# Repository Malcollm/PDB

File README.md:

# Humanoid Robot Power Distribution Board

This repository contains the power distribution board design for the Wiscohumanoids humanoid robot. The board distributes the main battery power to the robot’s high-current actuator system and generates regulated lower-voltage rails for compute, servos, sensors, and control electronics.

The PDB is designed around a 48 V main power system with onboard regulation for the robot’s auxiliary electronics.

## Project Overview

The power distribution board is responsible for taking the main battery input and safely distributing power throughout the robot. It includes high-current 48 V distribution, onboard buck converters, current sensing, precharge circuitry, and protection/disconnect circuitry.

The main goals of this board are:

- Distribute 48 V battery power to actuator rails
- Generate a 24 V compute rail
- Generate a 6 V servo rail for the robot hands
- Generate a 3.3 V rail for sensors and control electronics
- Monitor current on important power paths
- Limit inrush current during startup using precharge circuitry
- Separate actuator/servo power from compute/control power through protection and disconnect circuitry
- Protect the electrical system from voltage transients and fault conditions

## System Power Architecture

```text
Battery Input
    |
    |-- Precharge Circuit
    |
    |-- Main 48 V Power Rail
            |
            |-- Protection / Disconnect Circuitry
                    |
                    |-- Actuator / Servo Power Group
                    |       |
                    |       |-- 48 V Actuator Distribution
                    |       |
                    |       |-- 48 V to 6 V Buck Converter
                    |               |
                    |               |-- Hand Servos
                    |
                    |-- Compute / Control Power Group
                            |
                            |-- 48 V to 24 V Buck Converter
                            |       |
                            |       |-- Compute / Embedded Electronics
                            |
                            |-- 48 V to 3.3 V Buck Converter
                                    |
                                    |-- Sensors / Current Sensors / Control Logic
```

## Power Rails

| Rail | Purpose |
|---|---|
| 48 V | Main battery rail and actuator power distribution |
| 24 V | Compute and embedded electronics |
| 6 V | Servo motors in the robot hands |
| 3.3 V | Sensors, current sensors, and control logic |

## Major Board Features

### 48 V Actuator Distribution

The main power path distributes 48 V battery power to the robot’s actuator system. Because this rail carries the highest current on the board, the layout uses large copper pours, short current paths, and high-current connectors.

This section of the board is designed to minimize voltage drop and reduce heating under actuator load.

### Precharge Circuit

The board includes a precharge circuit to limit inrush current when the battery is connected. This is important because the board contains large bulk capacitance on the main 48 V rail.

During startup, the precharge path slowly charges the bulk capacitors before the main power path is fully enabled. This reduces stress on connectors, switches, relays, and other power components.

### Protection and Disconnect Circuitry

The PDB includes protection and disconnect circuitry that separates the main power system into two groups: the actuator/servo power group and the compute/control power group.

The actuator/servo group contains the 48 V actuator distribution and the 6 V hand servo rail. This group can be disconnected from the rest of the system so high-power motion components can be shut down independently.

The compute/control group contains the 12 V and 3.3 V rails. This allows the robot’s control electronics, sensors, and compute hardware to remain separated from the high-power actuator section.

This separation is important because it allows actuator power to be disabled while keeping control electronics available for monitoring, communication, and safe shutdown behavior.

Protection features include:

- Input transient voltage protection
- Precharge/inrush-current limiting
- Separation between actuator/servo power and compute/control power
- Reverse-current blocking where needed
- Current sensing for fault monitoring
- Support for external E-stop or main disconnect circuitry
- Bulk capacitance for load transients

### Current Sensing

Current sensors are included on important power paths so the robot can monitor how much current different parts of the system are drawing.

Current measurement is useful for:

- Detecting abnormal load conditions
- Debugging actuator behavior
- Estimating power usage
- Monitoring system health
- Adding future fault-detection logic

### Buck Converters

The PDB generates the lower-voltage rails from the main 48 V battery input using buck converters.

The onboard regulated rails are:

- 12 V for compute and embedded electronics
- 6 V for hand servos
- 3.3 V for sensors and control electronics

Each buck converter section includes the switching regulator circuit, input capacitance, output capacitance, feedback network, and supporting passives.

## Grounding

The board uses separate ground naming to keep high-current power paths and sensitive measurement/control paths organized.

Typical ground nets include:

| Net | Purpose |
|---|---|
| PGND | High-current power ground and switching converter return |
| AGND | Analog/sensor ground for feedback and current measurement circuits |

These grounds are not meant to be completely isolated systems. Instead, the separate names help control where large return currents flow and help keep sensor and feedback references cleaner.

## Design Status

This project is currently in development.

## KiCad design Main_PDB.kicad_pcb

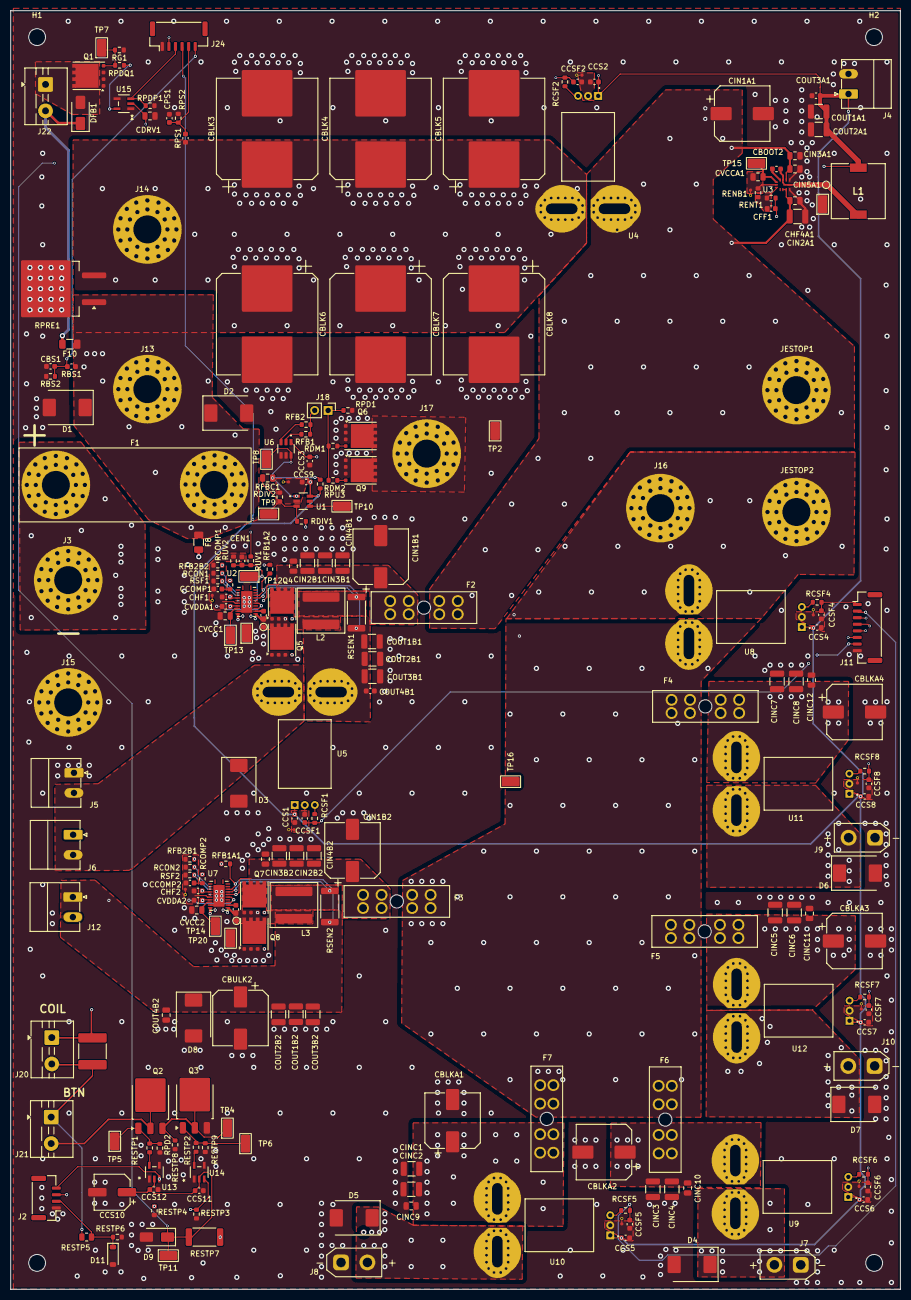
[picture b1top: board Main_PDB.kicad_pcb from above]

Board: 6 copper layers, 168.6 x 242.3 mm, 241 parts (0 on the bottom side), 105 nets.

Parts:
CBLK3, CBLK4, CBLK5, CBLK6, CBLK7, CBLK8: 470u; CP_Elec_18x22
CBLKA1, CBLKA2: 100uF; CP_Elec_10x10
CBLKA3, CBLKA4: 47uF; CP_Elec_10x10
CBOOT1, CBOOT3: 100n; C_0603_1608Metric
CBOOT2: 100nF; C_0603_1608Metric
CBS1: 100nF; C_0603_1608Metric
CBULK2: 100uF; CP_Elec_10x10
CCOMP1: 2nF; C_0603_1608Metric
CCOMP2: 2.7nF; C_0603_1608Metric
CCS1, CCS2, CCS3, CCS4, CCS5, CCS6, CCS7, CCS8, CCS9: 100n; C_0603_1608Metric
CCS10: 100uF 35V; CP_Elec_6.3x5.4
CCS11, CCS12: 100nF 50V; C_0603_1608Metric
CCSF1, CCSF2, CCSF4, CCSF5, CCSF6, CCSF7, CCSF8: 10n; C_0603_1608Metric
CDRV1: 1uF; C_0805_2012Metric
CEN1: 1nF; C_0603_1608Metric
CFF1: 22pF; C_0603_1608Metric
CHF1, CHF2: 22pF; C_0603_1608Metric
CHF4A1: 220nF; C_0805_2012Metric
CIN1A1, CIN1B1: 47uF; CP_Elec_10x10
CIN1B2: 100uF; CP_Elec_10x10
CIN2A1: 4.7uF; C_1210_3225Metric
CIN2B1, CIN2B2, CIN3B1, CIN3B2, CIN4B1, CIN4B2: 4.7u; C_1210_3225Metric
CIN3A1: 220nF; C_0805_2012Metric
CIN5A1, CIN5B1, CIN5B2: 100nF; C_0805_2012Metric
CINC1, CINC2, CINC3, CINC4, CINC5, CINC6, CINC7, CINC8: 4.7u; C_1210_3225Metric
CINC9, CINC10, CINC11, CINC12: 100nF; C_0805_2012Metric
COUT1A1, COUT2A1: 47uF; C_1210_3225Metric
COUT1B1, COUT1B2, COUT2B1, COUT2B2, COUT3B1, COUT3B2: 22uF; C_1210_3225Metric
COUT3A1, COUT4B1: 100nF; C_0603_1608Metric
COUT4B2: 100nF; C_0805_2012Metric
CPS1: 100nF; C_0603_1608Metric
CVCC1, CVCC2: 2.2u; C_0805_2012Metric
CVCCA1: 1uF; C_0805_2012Metric
CVDDA1, CVDDA2: 100n; C_0603_1608Metric
D1, D2, D3, D4, D5, D6, D7, D8: TVS; D_SMC
D9: 12V Zener 1W; D_SMA
D11: 3.3V Zener; D_SOD-123
DFB1: S1M; D_SMA
F1: Fuse; FUSE_BF1_M5_100A
F2, F3, F4, F5, F6, F7: LITTELFUSE_178.6165.0002
F8, F10: 0.5A; Fuse_1206_3216Metric
H1, H2, H3, H4: MountingHole_3.2mm_M3
J2: Conn_01x04; JST_GH_BM04B-GHS-TBT_1x04-1MP_P1.25mm_Vertical
J3: Conn_Batt_PWR; MountingHole_5.3mm_M5_Pad_Via_HP
J4: 3.3V Out; PhoenixContact_MC_1,5_2-G-3.81_1x02_P3.81mm_Horizontal
J5: 24V Out -> Jetson; PhoenixContact_MC_1,5_2-G-3.81_1x02_P3.81mm_Horizontal
J6: 24V Out -> USB-C-PD controller; PhoenixContact_MC_1,5_2-G-3.81_1x02_P3.81mm_Horizontal
J7, J8, J9, J10: Conn_01x02; AMASS_XT30UPB-F_1x02_P5.0mm_Vertical
J11: Conn_01x08; JST_GH_BM08B-GHS-TBT_1x08-1MP_P1.25mm_Vertical
J12: 6V Out; PhoenixContact_MC_1,5_2-G-3.81_1x02_P3.81mm_Horizontal
J13: PRECIN; MountingHole_5.3mm_M5_Pad_Via_HP
J14: PRECOUT; MountingHole_5.3mm_M5_Pad_Via_HP
J15: Conn_Batt_GND; MountingHole_5.3mm_M5_Pad_Via_HP
J16: Dump_Resistor_In; MountingHole_5.3mm_M5_Pad_Via_HP
J17: Dump_Resistor_Out; MountingHole_5.3mm_M5_Pad_Via_HP
J18: BC_Disconnect; PinHeader_1x02_P2.54mm_Vertical
J20: ESTOP Contactor Coil Control; TerminalBlock_MaiXu_MX126-5.0-02P_1x02_P5.00mm
J21: ESTOP Button (Normally Closed); TerminalBlock_MaiXu_MX126-5.0-02P_1x02_P5.00mm
J22: Precharge Contactor Coil Control; TerminalBlock_MaiXu_MX126-5.0-02P_1x02_P5.00mm
J24: Precharge Ctrl In; JST_GH_BM06B-GHS-TBT_1x06-1MP_P1.25mm_Vertical
JESTOP1: ESTOP_IN; MountingHole_5.3mm_M5_Pad_Via_HP
JESTOP2: ESTOP_OUT; MountingHole_5.3mm_M5_Pad_Via_HP
L1: 18uH; L_Sumida_CDRH104R
L2: 10uH; L_Coilcraft_XAL8080-XXX
L3: 4.7uH; L_Coilcraft_XAL8080-XXX
NT1, NT2, NT3, NT4, NT5, NT6, NT7, NT8, NT9, NT10, NT11: NetTie_2; NetTie_AGND_PGND_VIA
Q1, Q5, Q6, Q8, Q9: BSC070N10LS5ATMA1; VSONP-8-1EP_5x6_P1.27mm
Q2, Q3: NMOS IRFR220N; TO-252-3_TabPin2
Q4, Q7: BSC146N10LS5; VSONP-8-1EP_5x6_P1.27mm
RBS1: 100k; C_0603_1608Metric
RBS2: 3.9k; R_0603_1608Metric
RCOMP1: 19.1k; R_0603_1608Metric
RCOMP2: 12.1k; R_0603_1608Metric
RCON1, RCON2: 41.2k; R_0603_1608Metric
RCSF1, RCSF2, RCSF4, RCSF5, RCSF6, RCSF7, RCSF8: 1k; R_0603_1608Metric
RDIV1: 1M; R_0603_1608Metric
RDIV2: 24k; R_0603_1608Metric
RDM1, RDM2: 2.2R; R_0603_1608Metric
RENB1: 43.2k; R_0603_1608Metric
RENT1: 100k; R_0603_1608Metric
RESTP1, RESTP2: 100R; R_0603_1608Metric
RESTP3, RESTP4: 2.2k; R_0603_1608Metric
RESTP5: 100k; R_0805_2012Metric
RESTP6: 7.5k; R_0603_1608Metric
RESTP7: 4.7K 1W; R_2512_6332Metric
RESTP8, RESTP9: 100k; R_0603_1608Metric
RFB1, RFB2: 4.7R; R_0603_1608Metric
RFB1A1: 64.9k; R_0603_1608Metric
RFB1A2: 291k; R_0603_1608Metric
RFB2B1, RFB2B2: 10k; R_0603_1608Metric
RFBC1: 1.65M; C_0805_2012Metric
RG1: 100R; R_0603_1608Metric
RPD1, RPD2: 100k; R_0603_1608Metric
RPDP1: 100k; R_0603_1608Metric
RPDQ1: 100k; R_0603_1608Metric
RPRE1: 100; TO-263-2_Resistor
RPS1: 100k; C_0603_1608Metric
RPS2: 3.9k; R_0603_1608Metric
RPU3: 10k; R_0603_1608Metric
RSEN1, RSEN2: 0.004R; R_2512_6332Metric
RSF1, RSF2: 47k; R_0603_1608Metric
RUV1, RUV2: 100k; R_0603_1608Metric
TP1, TP2, TP3, TP4, TP5, TP6, TP7, TP8, TP9, TP10, TP11, TP12, TP13, TP14, TP15, TP16: Keystone 5015; TestPoint_Keystone_5015_Micro_Mini
TP17, TP18, TP19: SW probe pad; TestPoint_Pad_D1.0mm
TP20: PGND probe pad; TestPoint_Keystone_5015_Micro_Mini
U1: TLV3011AIDBVT; SOT95P280X145-6N
U2, U7: LM5148RGYR; QFN50P550X350X100-25N
U3: LMR36015ARNXR; RNX0012B
U4, U5, U8, U9, U10, U11, U12: ACS758LCB-100B-PFF-T; XDCR_ACS758LCB-100U-PFF-T
U6: UCC27511DBVR; SOT95P280X145-6N
U13, U14, U15: MCP1402T-E/OT; SOT-23-5_MC_MCH
ZV50K2220801NIR1: Varistor; C_2220_5750Metric

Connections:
+3.3V: CCS1.1, CCS2.2, CCS4.2, CCS5.1, CCS6.1, CCS7.1, CCS8.1, CCS9.1, CFF1.1, COUT1A1.1, COUT2A1.1, COUT3A1.1, J4.1, J24.2, L1.2, RENT1.1, RPU3.2, U1.6 (V+), U4.1 (VCC), U5.1 (VCC), U8.1 (VCC), U9.1 (VCC), U10.1 (VCC), U11.1 (VCC), U12.1 (VCC)
+6V: CBULK2.1, CCS3.1, COUT1B2.1, COUT2B2.1, COUT3B2.1, COUT4B2.1, D8.1 (K), J12.1, RFB1A1.2, RSEN2.2, U6.1 (VDD), U7.21 (VOUT)
+6V_IND: L3.2, RSEN2.1, U7.20 (ISNS+)
+24V: D3.1 (K), J5.2, J6.2, U5.5 (IP-), U5.5_1 (IP-), U5.5_2 (IP-), U5.5_3 (IP-), U5.5_4 (IP-), U5.5_5 (IP-), U5.5_6 (IP-), U5.5_7 (IP-), U5.5_8 (IP-), U5.5_9 (IP-), U5.5_10 (IP-), U5.5_11 (IP-), U5.5_12 (IP-), U5.5_13 (IP-), U5.5_14 (IP-), U5.5_15 (IP-), U5.5_16 (IP-)
+48V_BATT: F1.1, J3.1 (Pin_1_1)
/3V3_SW: CBOOT2.2, L1.1, TP19.1 (1_1), U3.3 (NC), U3.12 (SW)
/3V3_VCC: CVCCA1.2, TP15.1 (1_1), U3.5 (VCC)
/6V_FUSE: CIN1B2.1, CIN2B2.2, CIN3B2.2, CIN4B2.2, CIN5B2.2, F3.2_1, F3.2_2, F3.2_3, F3.2_4, Q7.3 (D), U7.12 (VIN), U7.19 (EN)
/6V_NMOS: CBOOT3.1, L3.1, Q7.1 (S), Q8.3 (D), TP18.1 (1_1), U7.14 (SW)
/6V_VCC: CVCC2.1, TP14.1 (1_1), U7.9 (VCC)
/12V_BIAS: CCS10.1, CCS11.2, CCS12.2, CDRV1.1, D9.1 (K), RESTP7.2, TP11.1 (1_1), U13.2 (VDD), U14.2 (VDD), U15.2 (VDD)
/24V_EN: CEN1.1, RUV1.2, RUV2.1, TP12.1 (1_1), U2.19 (EN)
/24V_EN_IN: J24.4, RUV1.1
/24V_FUSE: CIN1B1.1, CIN2B1.2, CIN3B1.2, CIN4B1.2, CIN5B1.2, F2.2_1, F2.2_2, F2.2_3, F2.2_4, Q4.3 (D), U2.12 (VIN)
/24V_IND: L2.2, RSEN1.1, U2.20 (ISNS+)
/24V_NMOS: CBOOT1.2, L2.1, Q4.1 (S), Q5.3 (D), TP17.1 (1_1), U2.14 (SW)
/24V_SEN: COUT1B1.1, COUT2B1.1, COUT3B1.1, COUT4B1.1, RFB1A2.2, RSEN1.2, U2.21 (VOUT), U5.4 (IP+), U5.4_1 (IP+), U5.4_2 (IP+), U5.4_3 (IP+), U5.4_4 (IP+), U5.4_5 (IP+), U5.4_6 (IP+), U5.4_7 (IP+), U5.4_8 (IP+), U5.4_9 (IP+), U5.4_10 (IP+), U5.4_11 (IP+), U5.4_12 (IP+), U5.4_13 (IP+), U5.4_14 (IP+), U5.4_15 (IP+), U5.4_16 (IP+)
/24V_VCC: CVCC1.1, TP13.1 (1_1), U2.9 (VCC)
/48V_ACT: F3.1_1, F3.1_2, F3.1_3, F3.1_4, F4.1_1, F4.1_2, F4.1_3, F4.1_4, F5.1_1, F5.1_2, F5.1_3, F5.1_4, F6.1_1, F6.1_2, F6.1_3, F6.1_4, F7.1_1, F7.1_2, F7.1_3, F7.1_4, U8.5 (IP-), U8.5_1 (IP-), U8.5_2 (IP-), U8.5_3 (IP-), U8.5_4 (IP-), U8.5_5 (IP-), U8.5_6 (IP-), U8.5_7 (IP-), U8.5_8 (IP-), U8.5_9 (IP-), U8.5_10 (IP-), U8.5_11 (IP-), U8.5_12 (IP-), U8.5_13 (IP-), U8.5_14 (IP-), U8.5_15 (IP-), U8.5_16 (IP-)
/48V_ACT1: D5.1 (K), J8.2, U10.5 (IP-), U10.5_1 (IP-), U10.5_2 (IP-), U10.5_3 (IP-), U10.5_4 (IP-), U10.5_5 (IP-), U10.5_6 (IP-), U10.5_7 (IP-), U10.5_8 (IP-), U10.5_9 (IP-), U10.5_10 (IP-), U10.5_11 (IP-), U10.5_12 (IP-), U10.5_13 (IP-), U10.5_14 (IP-), U10.5_15 (IP-), U10.5_16 (IP-)
/48V_ACT1_FUSE: CBLKA1.1, CINC1.2, CINC2.2, CINC9.1, F7.2_1, F7.2_2, F7.2_3, F7.2_4, U10.4 (IP+), U10.4_1 (IP+), U10.4_2 (IP+), U10.4_3 (IP+), U10.4_4 (IP+), U10.4_5 (IP+), U10.4_6 (IP+), U10.4_7 (IP+), U10.4_8 (IP+), U10.4_9 (IP+), U10.4_10 (IP+), U10.4_11 (IP+), U10.4_12 (IP+), U10.4_13 (IP+), U10.4_14 (IP+), U10.4_15 (IP+), U10.4_16 (IP+)
/48V_ACT2: D4.1 (K), J7.2, U9.5 (IP-), U9.5_1 (IP-), U9.5_2 (IP-), U9.5_3 (IP-), U9.5_4 (IP-), U9.5_5 (IP-), U9.5_6 (IP-), U9.5_7 (IP-), U9.5_8 (IP-), U9.5_9 (IP-), U9.5_10 (IP-), U9.5_11 (IP-), U9.5_12 (IP-), U9.5_13 (IP-), U9.5_14 (IP-), U9.5_15 (IP-), U9.5_16 (IP-)
/48V_ACT2_FUSE: CBLKA2.1, CINC3.2, CINC4.2, CINC10.1, F6.2_1, F6.2_2, F6.2_3, F6.2_4, U9.4 (IP+), U9.4_1 (IP+), U9.4_2 (IP+), U9.4_3 (IP+), U9.4_4 (IP+), U9.4_5 (IP+), U9.4_6 (IP+), U9.4_7 (IP+), U9.4_8 (IP+), U9.4_9 (IP+), U9.4_10 (IP+), U9.4_11 (IP+), U9.4_12 (IP+), U9.4_13 (IP+), U9.4_14 (IP+), U9.4_15 (IP+), U9.4_16 (IP+)
/48V_ACT3: D7.1 (K), J10.2, U12.5 (IP-), U12.5_1 (IP-), U12.5_2 (IP-), U12.5_3 (IP-), U12.5_4 (IP-), U12.5_5 (IP-), U12.5_6 (IP-), U12.5_7 (IP-), U12.5_8 (IP-), U12.5_9 (IP-), U12.5_10 (IP-), U12.5_11 (IP-), U12.5_12 (IP-), U12.5_13 (IP-), U12.5_14 (IP-), U12.5_15 (IP-), U12.5_16 (IP-)
/48V_ACT3_FUSE: CBLKA3.1, CINC5.2, CINC6.2, CINC11.1, F5.2_1, F5.2_2, F5.2_3, F5.2_4, U12.4 (IP+), U12.4_1 (IP+), U12.4_2 (IP+), U12.4_3 (IP+), U12.4_4 (IP+), U12.4_5 (IP+), U12.4_6 (IP+), U12.4_7 (IP+), U12.4_8 (IP+), U12.4_9 (IP+), U12.4_10 (IP+), U12.4_11 (IP+), U12.4_12 (IP+), U12.4_13 (IP+), U12.4_14 (IP+), U12.4_15 (IP+), U12.4_16 (IP+)
/48V_ACT4: D6.1 (K), J9.2, U11.5 (IP-), U11.5_1 (IP-), U11.5_2 (IP-), U11.5_3 (IP-), U11.5_4 (IP-), U11.5_5 (IP-), U11.5_6 (IP-), U11.5_7 (IP-), U11.5_8 (IP-), U11.5_9 (IP-), U11.5_10 (IP-), U11.5_11 (IP-), U11.5_12 (IP-), U11.5_13 (IP-), U11.5_14 (IP-), U11.5_15 (IP-), U11.5_16 (IP-)
/48V_ACT4_FUSE: CBLKA4.1, CINC7.2, CINC8.2, CINC12.1, F4.2_1, F4.2_2, F4.2_3, F4.2_4, U11.4 (IP+), U11.4_1 (IP+), U11.4_2 (IP+), U11.4_3 (IP+), U11.4_4 (IP+), U11.4_5 (IP+), U11.4_6 (IP+), U11.4_7 (IP+), U11.4_8 (IP+), U11.4_9 (IP+), U11.4_10 (IP+), U11.4_11 (IP+), U11.4_12 (IP+), U11.4_13 (IP+), U11.4_14 (IP+), U11.4_15 (IP+), U11.4_16 (IP+)
/48V_ESTOP: J16.1 (Pin_1_1), JESTOP2.1 (Pin_1_1), RDIV1.1, U8.4 (IP+), U8.4_1 (IP+), U8.4_2 (IP+), U8.4_3 (IP+), U8.4_4 (IP+), U8.4_5 (IP+), U8.4_6 (IP+), U8.4_7 (IP+), U8.4_8 (IP+), U8.4_9 (IP+), U8.4_10 (IP+), U8.4_11 (IP+), U8.4_12 (IP+), U8.4_13 (IP+), U8.4_14 (IP+), U8.4_15 (IP+), U8.4_16 (IP+)
/48V_FUSE: D1.1 (K), D2.1 (K), F1.2, F8.1, F10.1, J13.1 (Pin_1_1), RBS1.1, RPRE1.1
/48V_MAIN: CHF4A1.1, CIN1A1.1, CIN2A1.1, CIN3A1.1, CIN5A1.1, F2.1_1, F2.1_2, F2.1_3, F2.1_4, JESTOP1.1 (Pin_1_1), U3.2 (VIN), U3.9 (EN), U3.10 (VIN), U4.5 (IP-), U4.5_1 (IP-), U4.5_2 (IP-), U4.5_3 (IP-), U4.5_4 (IP-), U4.5_5 (IP-), U4.5_6 (IP-), U4.5_7 (IP-), U4.5_8 (IP-), U4.5_9 (IP-), U4.5_10 (IP-), U4.5_11 (IP-), U4.5_12 (IP-), U4.5_13 (IP-), U4.5_14 (IP-), U4.5_15 (IP-), U4.5_16 (IP-)
/48V_PRECH: CBLK3.1, CBLK4.1, CBLK5.1, CBLK6.1, CBLK7.1, CBLK8.1, J14.1 (Pin_1_1), RPRE1.2, RPS1.1, U4.4 (IP+), U4.4_1 (IP+), U4.4_2 (IP+), U4.4_3 (IP+), U4.4_4 (IP+), U4.4_5 (IP+), U4.4_6 (IP+), U4.4_7 (IP+), U4.4_8 (IP+), U4.4_9 (IP+), U4.4_10 (IP+), U4.4_11 (IP+), U4.4_12 (IP+), U4.4_13 (IP+), U4.4_14 (IP+), U4.4_15 (IP+), U4.4_16 (IP+)
/Act_rail_curr: CCSF4.2, J11.1, RCSF4.2
/BATT_SENSE: CBS1.1, J24.6, RBS1.2, RBS2.1
/Com_cur: CCSF1.2, J11.7, RCSF1.2
/DUMP_REF: TP10.1 (1_1), U1.4 (IN-), U1.5 (REF)
/DUMP_SENSE: RDIV1.2, RDIV2.1, RFBC1.2, TP9.1 (1_1), U1.3 (IN+)
/DUMP_TRIG: RFBC1.1, RPU3.1, TP8.1 (1_1), U1.1 (OUT), U6.6 (IN+)
/D_R_OUT: J17.1 (Pin_1_1), Q6.3 (D), Q9.3 (D)
/ESTOP_EN1: J2.4, RESTP4.2, U13.3 (IN)
/ESTOP_EN2: J2.3, RESTP3.1, U14.3 (IN)
/ESTOP_FB: D11.1 (K), J2.2, RESTP5.2, RESTP6.1
/ESTOP_FET_MID: Q2.3 (S), Q3.2 (D), RPD2.2, TP4.1 (1_1)
/ESTOP_G1: Q2.1 (G), RESTP1.1, RESTP8.1, TP5.1 (1_1)
/ESTOP_G2: Q3.1 (G), RESTP2.1, RESTP9.2, TP6.1 (1_1)
/Main_curr: CCSF2.2, J11.6, RCSF2.2
/PRECH_EN: J24.3, RPDP1.1, U15.3 (IN)
/PRECH_GATE: Q1.2 (G), RG1.1, RPDQ1.1, TP7.1 (1_1)
/PRECH_SENSE: CPS1.1, J24.5, RPS1.2, RPS2.1
AGND: CCS2.1, CCSF2.1, NT10.1, U4.2 (GND)
AGND1: CCS9.2, NT1.1, RDIV2.2, U1.2 (V-)
AGND2: CCOMP1.2, CEN1.2, CHF1.2, CVDDA1.1, NT2.1, RCON1.1, RFB2B2.1, RSF1.1, RUV2.2, U2.7 (AGND), U2.16 (VCCX), U2.18 (PFM/SYNC)
AGND3: CCOMP2.2, CHF2.2, CVDDA2.1, NT3.1, RCON2.1, RFB2B1.1, RSF2.1, U7.7 (AGND), U7.16 (VCCX), U7.18 (PFM/SYNC)
AGND4: CCS1.2, CCSF1.1, NT4.1, U5.2 (GND)
AGND5: CVCCA1.1, NT5.1, RENB1.2, U3.6 (AGND)
AGND6: CCS4.1, CCSF4.1, NT6.1, U8.2 (GND)
AGND7: CCS5.2, CCSF5.1, NT7.1, U10.2 (GND)
AGND8: CCS6.2, CCSF6.1, NT8.1, U9.2 (GND)
AGND9: CCS7.2, CCSF7.1, NT9.1, U12.2 (GND)
AGND10: CCS8.2, CCSF8.1, NT11.1, U11.2 (GND)
unnamed: CCOMP1.1, RCOMP1.2
unnamed: CCOMP2.1, RCOMP2.2
unnamed: DFB1.2 (A), J22.1, Q1.3 (D)
unnamed: DFB1.1 (K), F10.2, J22.2
unnamed: CCSF5.2, J11.2, RCSF5.2
unnamed: CCSF6.2, J11.3, RCSF6.2
unnamed: CCSF7.2, J11.4, RCSF7.2
unnamed: CCSF8.2, J11.5, RCSF8.2
unnamed: J18.1, RDM1.2, RDM2.2, RPD1.2
unnamed: J18.2, RFB1.2, RFB2.2
unnamed: F8.2, J20.1, RESTP7.1, ZV50K2220801NIR1.2
unnamed: J20.2, J21.1, RESTP5.1, ZV50K2220801NIR1.1
unnamed: J21.2, Q2.2 (D)
unnamed: Q4.2 (G), U2.13 (HO)
unnamed: Q5.2 (G), U2.11 (LO)
unnamed: Q6.2 (G), RDM1.1
unnamed: Q7.2 (G), U7.13 (HO)
unnamed: Q8.2 (G), U7.11 (LO)
unnamed: Q9.2 (G), RDM2.1
unnamed: CBOOT1.1, U2.15 (CBOOT)
unnamed: RCON1.2, U2.3 (CNFG)
unnamed: CHF1.1, RCOMP1.1, U2.5 (EXTCOMP)
unnamed: RFB1A2.1, RFB2B2.2, U2.6 (FB)
unnamed: RSF1.2, U2.4 (RT)
unnamed: CVDDA1.2, U2.8 (VDDA)
unnamed: CBOOT2.1, U3.4 (BST)
unnamed: CFF1.2, RENB1.1, RENT1.2, U3.7 (FB)
unnamed: RCSF2.1, U4.3 (VIOUT)
unnamed: RCSF1.1, U5.3 (VIOUT)
unnamed: RFB1.1, U6.2 (OUTH)
unnamed: RFB2.1, U6.3 (OUTL)
unnamed: CBOOT3.2, U7.15 (CBOOT)
unnamed: RCON2.2, U7.3 (CNFG)
unnamed: CHF2.1, RCOMP2.1, U7.5 (EXTCOMP)
unnamed: RFB1A1.1, RFB2B1.2, U7.6 (FB)
unnamed: RSF2.2, U7.4 (RT)
unnamed: CVDDA2.2, U7.8 (VDDA)
unnamed: RCSF4.1, U8.3 (VIOUT)
unnamed: RCSF6.1, U9.3 (VIOUT)
unnamed: RCSF5.1, U10.3 (VIOUT)
unnamed: RCSF8.1, U11.3 (VIOUT)
unnamed: RCSF7.1, U12.3 (VIOUT)
unnamed: RESTP1.2, U13.5 (OUT)
unnamed: RESTP2.2, U14.5 (OUT)
unnamed: RG1.2, U15.5 (OUT)
PGND: CBLK3.2, CBLK4.2, CBLK5.2, CBLK6.2, CBLK7.2, CBLK8.2, CBLKA1.2, CBLKA2.2, CBLKA3.2, CBLKA4.2, CBS1.2, CBULK2.2, CCS3.2, CCS10.2, CCS11.1, CCS12.1, CDRV1.2, CHF4A1.2, CIN1A1.2, CIN1B1.2, CIN1B2.2, CIN2A1.2, CIN2B1.1, CIN2B2.1, CIN3A1.2, CIN3B1.1, CIN3B2.1, CIN4B1.1, CIN4B2.1, CIN5A1.2, CIN5B1.1, CIN5B2.1, CINC1.1, CINC2.1, CINC3.1, CINC4.1, CINC5.1, CINC6.1, CINC7.1, CINC8.1, CINC9.2, CINC10.2, CINC11.2, CINC12.2, COUT1A1.2, COUT1B1.2, COUT1B2.2, COUT2A1.2, COUT2B1.2, COUT2B2.2, COUT3A1.2, COUT3B1.2, COUT3B2.2, COUT4B1.2, COUT4B2.2, CPS1.2, CVCC1.2, CVCC2.2, D1.2 (A), D2.2 (A), D3.2 (A), D4.2 (A), D5.2 (A), D6.2 (A), D7.2 (A), D8.2 (A), D9.2 (A), D11.2 (A), J2.1, J4.2, J5.1, J6.1, J7.1, J8.1, J9.1, J10.1, J11.8, J12.2, J15.1 (Pin_1_1), J24.1, NT1.2, NT2.2, NT3.2, NT4.2, NT5.2, NT6.2, NT7.2, NT8.2, NT9.2, NT10.2, NT11.2, Q1.1 (S), Q3.3 (S), Q5.1 (S), Q6.1 (S), Q8.1 (S), Q9.1 (S), RBS2.2, RESTP3.2, RESTP4.1, RESTP6.2, RESTP8.2, RESTP9.1, RPD1.1, RPD2.1, RPDP1.2, RPDQ1.2, RPRE1.3 (GND_3), RPS2.2, TP1.1 (1_1), TP2.1 (1_1), TP3.1 (1_1), TP16.1 (1_1), TP20.1 (1_1), U2.10 (PGND), U2.25 (EP), U3.1 (PGND), U3.11 (PGND), U6.4 (GND), U6.5 (IN-), U7.10 (PGND), U7.25 (EP), U13.1 (GND), U13.4 (GND), U14.1 (GND), U14.4 (GND), U15.1 (GND), U15.4 (GND)

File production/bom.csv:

Designator,Footprint,Quantity,Value,LCSC Part #
"CBLK3, CBLK4, CBLK5, CBLK6, CBLK7, CBLK8",CP_Elec_18x22,6,470u,C3829592
"CBLKA1, CBLKA2, CBULK2, CIN1B2",CP_Elec_10x10,4,100uF,C5246576
"CBLKA3, CBLKA4, CIN1A1, CIN1B1",CP_Elec_10x10,4,47uF,C164068
"CBOOT1, CBOOT3, CCS1, CCS2, CCS3, CCS4, CCS5, CCS6, CCS7, CCS8, CCS9, CVDDA1, CVDDA2",0603,13,100n,C1591
"CBOOT2, CBS1, COUT3A1, COUT4B1, CPS1",0603,5,100nF,C1591
CCOMP1,0603,1,2nF,C1870141
CCOMP2,0603,1,2.7nF,C77034
CCS10,CP_Elec_6.3x5.4,1,100uF 35V,C5138965
"CCS11, CCS12",0603,2,100nF 50V,C1591
"CCSF1, CCSF2, CCSF4, CCSF5, CCSF6, CCSF7, CCSF8",0603,7,10n,C519406
"CDRV1, CVCCA1",0805,2,1uF,C24123
CEN1,0603,1,1nF,C1588
"CFF1, CHF1, CHF2",0603,3,22pF,C1653
"CHF4A1, CIN3A1",0805,2,220nF,C513710
CIN2A1,1210,1,4.7uF,C381466
"CIN2B1, CIN2B2, CIN3B1, CIN3B2, CIN4B1, CIN4B2, CINC1, CINC2, CINC3, CINC4, CINC5, CINC6, CINC7, CINC8",1210,14,4.7u,C381466
"CIN5A1, CIN5B1, CIN5B2, CINC10, CINC11, CINC12, CINC9, COUT4B2",0805,8,100nF,C344180
"COUT1A1, COUT2A1",1210,2,47uF,C77101
"COUT1B1, COUT1B2, COUT2B1, COUT2B2, COUT3B1, COUT3B2",1210,6,22uF,C778721
"CVCC1, CVCC2",0805,2,2.2u,C377773
"D1, D2, D4, D5, D6, D7",D_SMC,6,TVS,C438117
D11,D_SOD-123,1,3.3V Zener,C235771
D3,D_SMC,1,TVS,C438106
D8,D_SMC,1,TVS,C492903
D9,D_SMA,1,12V Zener 1W,C110523
DFB1,D_SMA,1,S1M,C155378
F1,FUSE_BF1_M5_100A,1,Fuse,
"F10, F8",1206,2,0.5A,
"F2, F3, F4, F5, F6, F7",LITTELFUSE_178.6165.0002,6,~,
"J10, J7, J8, J9",AMASS_XT30UPB-F_1x02_P5.0mm_Vertical,4,Conn_01x02,C108769
J11,JST_GH_BM08B-GHS-TBT_1x08-1MP_P1.25mm_Vertical,1,Conn_01x08,C133062
J12,"PhoenixContact_MC_1,5_2-G-3.81_1x02_P3.81mm_Horizontal",1,6V Out,C480537
J13,MountingHole_5.3mm_M5_Pad_Via_HP,1,PRECIN,
J14,MountingHole_5.3mm_M5_Pad_Via_HP,1,PRECOUT,
J15,MountingHole_5.3mm_M5_Pad_Via_HP,1,Conn_Batt_GND,
J16,MountingHole_5.3mm_M5_Pad_Via_HP,1,Dump_Resistor_In,
J17,MountingHole_5.3mm_M5_Pad_Via_HP,1,Dump_Resistor_Out,
J18,PinHeader_1x02_P2.54mm_Vertical,1,BC_Disconnect,C492401
J2,JST_GH_BM04B-GHS-TBT_1x04-1MP_P1.25mm_Vertical,1,Conn_01x04,C161692
J20,TerminalBlock_MaiXu_MX126-5.0-02P_1x02_P5.00mm,1,ESTOP Contactor Coil Control,C5188434
J21,TerminalBlock_MaiXu_MX126-5.0-02P_1x02_P5.00mm,1,ESTOP Button (Normally Closed),C5188434
J22,TerminalBlock_MaiXu_MX126-5.0-02P_1x02_P5.00mm,1,Precharge Contactor Coil Control,C5188434
J24,JST_GH_BM06B-GHS-TBT_1x06-1MP_P1.25mm_Vertical,1,Precharge Ctrl In,C189892
J3,MountingHole_5.3mm_M5_Pad_Via_HP,1,Conn_Batt_PWR,
J4,"PhoenixContact_MC_1,5_2-G-3.81_1x02_P3.81mm_Horizontal",1,3.3V Out,C480537
J5,"PhoenixContact_MC_1,5_2-G-3.81_1x02_P3.81mm_Horizontal",1,24V Out -> Jetson,C480537
J6,"PhoenixContact_MC_1,5_2-G-3.81_1x02_P3.81mm_Horizontal",1,24V Out -> USB-C-PD controller,C480537
JESTOP1,MountingHole_5.3mm_M5_Pad_Via_HP,1,ESTOP_IN,
JESTOP2,MountingHole_5.3mm_M5_Pad_Via_HP,1,ESTOP_OUT,
L1,L_Sumida_CDRH104R,1,18uH,C225049
L2,L_Coilcraft_XAL8080-XXX,1,10uH,C49261520
L3,L_Coilcraft_XAL8080-XXX,1,4.7uH,C7432408
"NT1, NT10, NT11, NT2, NT3, NT4, NT5, NT6, NT7, NT8, NT9",NetTie_AGND_PGND_VIA,11,NetTie_2,
"Q1, Q5, Q6, Q8, Q9",VSONP-8-1EP_5x6_P1.27mm,5,BSC070N10LS5ATMA1,C3278731
"Q2, Q3",TO-252-3_TabPin2,2,NMOS IRFR220N,C506577
"Q4, Q7",VSONP-8-1EP_5x6_P1.27mm,2,BSC146N10LS5,C534417
"RBS1, RENT1, RUV1, RUV2",0603,4,100k,C122538
"RBS2, RPS2",0603,2,3.9k,C473237
RCOMP1,0603,1,19.1k,C149926
RCOMP2,0603,1,12.1k,C705723
"RCON1, RCON2",0603,2,41.2k,C705776
"RCSF1, RCSF2, RCSF4, RCSF5, RCSF6, RCSF7, RCSF8",0603,7,1k,C14676
RDIV1,0603,1,1M,C326730
RDIV2,0603,1,24k,C217904
"RDM1, RDM2",0603,2,2.2R,C22939
RENB1,0603,1,43.2k,C861404
"RESTP1, RESTP2, RG1",0603,3,100R,C22775
"RESTP3, RESTP4",0603,2,2.2k,C4190
RESTP5,0805,1,100k,C96346
RESTP6,0603,1,7.5k,C23234
RESTP7,2512,1,4.7K 1W,C163339
"RESTP8, RESTP9, RPD1, RPD2, RPDP1, RPDQ1",0603,6,100k,C14675
"RFB1, RFB2",0603,2,4.7R,C23164
RFB1A1,0603,1,64.9k,C861510
RFB1A2,0603,1,291k,C861285
"RFB2B1, RFB2B2, RPU3",0603,3,10k,C95204
RFBC1,0805,1,1.65M,C218412
RPRE1,TO-263-2_Resistor,1,100,C26159126
RPS1,0603,1,100k, C122538
"RSEN1, RSEN2",2512,2,0.004R,C105388
"RSF1, RSF2",0603,2,47k,C218044
"TP1, TP10, TP11, TP12, TP13, TP14, TP15, TP16, TP2, TP3, TP4, TP5, TP6, TP7, TP8, TP9",TestPoint_Keystone_5015_Micro_Mini,16,Keystone 5015,C2906768
TP20,TestPoint_Keystone_5015_Micro_Mini,1,PGND probe pad,
U1,SOT95P280X145-6N,1,TLV3011AIDBVT,C2867795
"U10, U11, U12, U4, U5, U8, U9",XDCR_ACS758LCB-100U-PFF-T,7,ACS758LCB-100B-PFF-T,C82405
"U13, U14, U15",SOT-23-5_MC_MCH,3,MCP1402T-E/OT,C128573
"U2, U7",QFN50P550X350X100-25N,2,LM5148RGYR,C7470701
U3,RNX0012B,1,LMR36015ARNXR,C1850345
U6,SOT95P280X145-6N,1,UCC27511DBVR,C191027
ZV50K2220801NIR1,2220,1,Varistor,C53286339

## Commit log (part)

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2026-04-06 Added input cap at 48->24 comp buck
2026-04-10 Converted 24V actuator rails to 48V actuator rails
2026-04-10 V10 change
2026-04-11 Test V10
2026-04-11 Added Pre charge tag
2026-04-11 test
2026-04-11 LM5143 48-24V Buck Interleaved Buck Converter
    KiCad Files and relevant Texas Instruments Documentation
2026-04-12 File added for master
2026-04-12 Resized page
2026-04-18 Added regen protection
2026-04-18 Added updated 48 to 3.3v converter
2026-04-18 small clean up
2026-04-19 Added regen MOSFET drivers
2026-04-19 Added PMOS to precharge
2026-04-19 schematic labeling
2026-04-19 Changed main buck
2026-04-21 Started on high side fet driver for precharge
2026-04-21 48V -> 6V buck added
2026-04-21 Fixed 48V -> 6V buck power source
2026-04-23 restructured actuator rails
2026-04-23 48->6 power conection update
2026-04-24 Added precharge high side nmos controler
2026-04-24 Changed current sensors to 3.3V
2026-04-26 tvs diodes for overvoltage protection at the battery input
2026-04-26 added TVS diodes for overvoltage protection for each actuator rail output and also the 24v and 6v rail outputs
2026-04-26 tvs diodes update
2026-04-26 caps
2026-04-27 Changed 48->24 to 48->12
2026-04-28 Format change
2026-04-29 updated component values for 6v convert
2026-04-29 updated grounds for converters, need to double check grounds for current sense. Did not adjust grounds on actuators/precharge. Added pull up resistor on 6v PG output.
2026-04-29 changed ground for ext comp circuit
2026-04-29 added thermistors in lower left hand side, exact values, quantity,and need for more specific measurement will be determined during testing/tracing.
2026-04-29 Grounding and inductor and output caps on 12V buck
2026-04-29 Added compute buck cap
2026-04-29 Added input caps to 6V buck
2026-04-30 Thermistors edit
2026-04-30 misc
2026-05-31 TVS diode grounding changes
2026-06-01 input/output caps on 3.3V rail update
2026-06-01 Revisions for 3.3V buck + Added footprints
2026-06-02 Started updating 48->12 buck footprints (caps and res)
2026-06-02 Added input cap to 48->12 buck
2026-06-02 Changed sf and ripple current %
2026-06-02 Added footprints for ics in 12V buck
2026-06-05 48->6V buck updates
2026-06-05 output caps on 6V rail
2026-06-05 test; no changes
2026-06-05 FET footprints added
2026-06-05 Added fuse holder footprints
2026-06-05 Setup main pour topology
2026-06-05 Added star point
2026-06-07 added footprints onto the PCB
2026-06-14 input caps on actuator rails updated with footprints
2026-06-14 Fixing Kicad crash
2026-06-14 Bulk caps and low pass filting on CS output
2026-06-14 back current updates + footprints
2026-06-15 Changed prechage to relay based system and added footprints to PCB
2026-06-16 added estop coil control circuit
2026-06-24 Added nets to all high current connections
2026-06-24 PCB for bulk caps and main curr sen
2026-06-25 PCB buck caps and 3.3V buck
2026-06-25 Adj vias in 3.3V buck
2026-06-25 redid 3.3 buck layout on pcb
2026-06-25 edited pgnd (upper) on 3.3V buck
2026-06-25 added additonal vias in pgnd pour
2026-06-26 bulk caps relayout and added power pours on bottom layer
2026-06-26 silkscreen updates
2026-06-27 fixed grounding error
2026-06-28 Revise README to include detailed project information
    Expanded the README to provide detailed information about the Humanoid Robot Power Distribution Board, including project overview, system architecture, power rails, major features, and design status.
2026-06-30 adj decoupling caps placements
